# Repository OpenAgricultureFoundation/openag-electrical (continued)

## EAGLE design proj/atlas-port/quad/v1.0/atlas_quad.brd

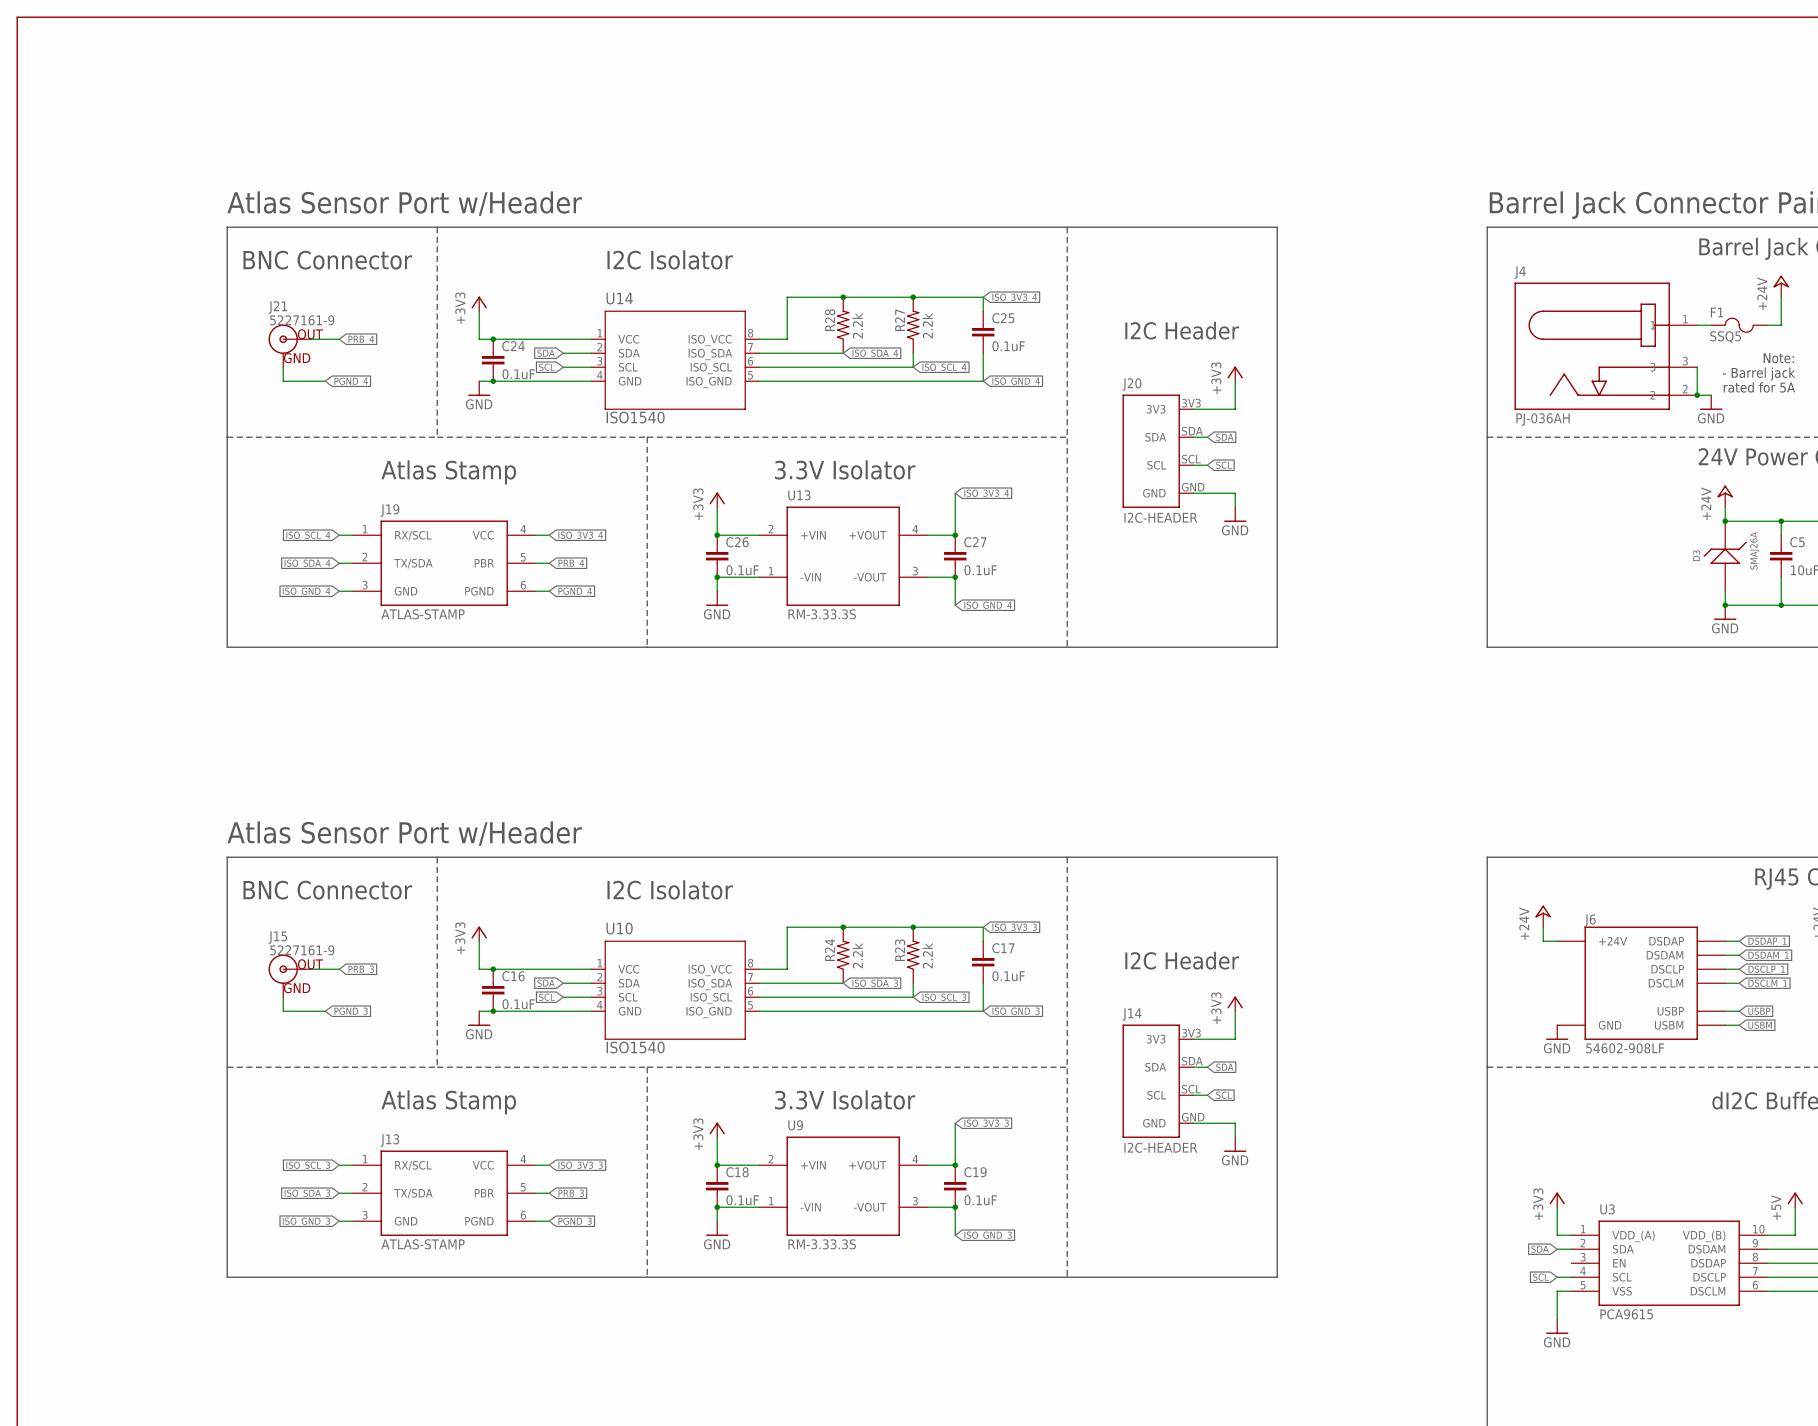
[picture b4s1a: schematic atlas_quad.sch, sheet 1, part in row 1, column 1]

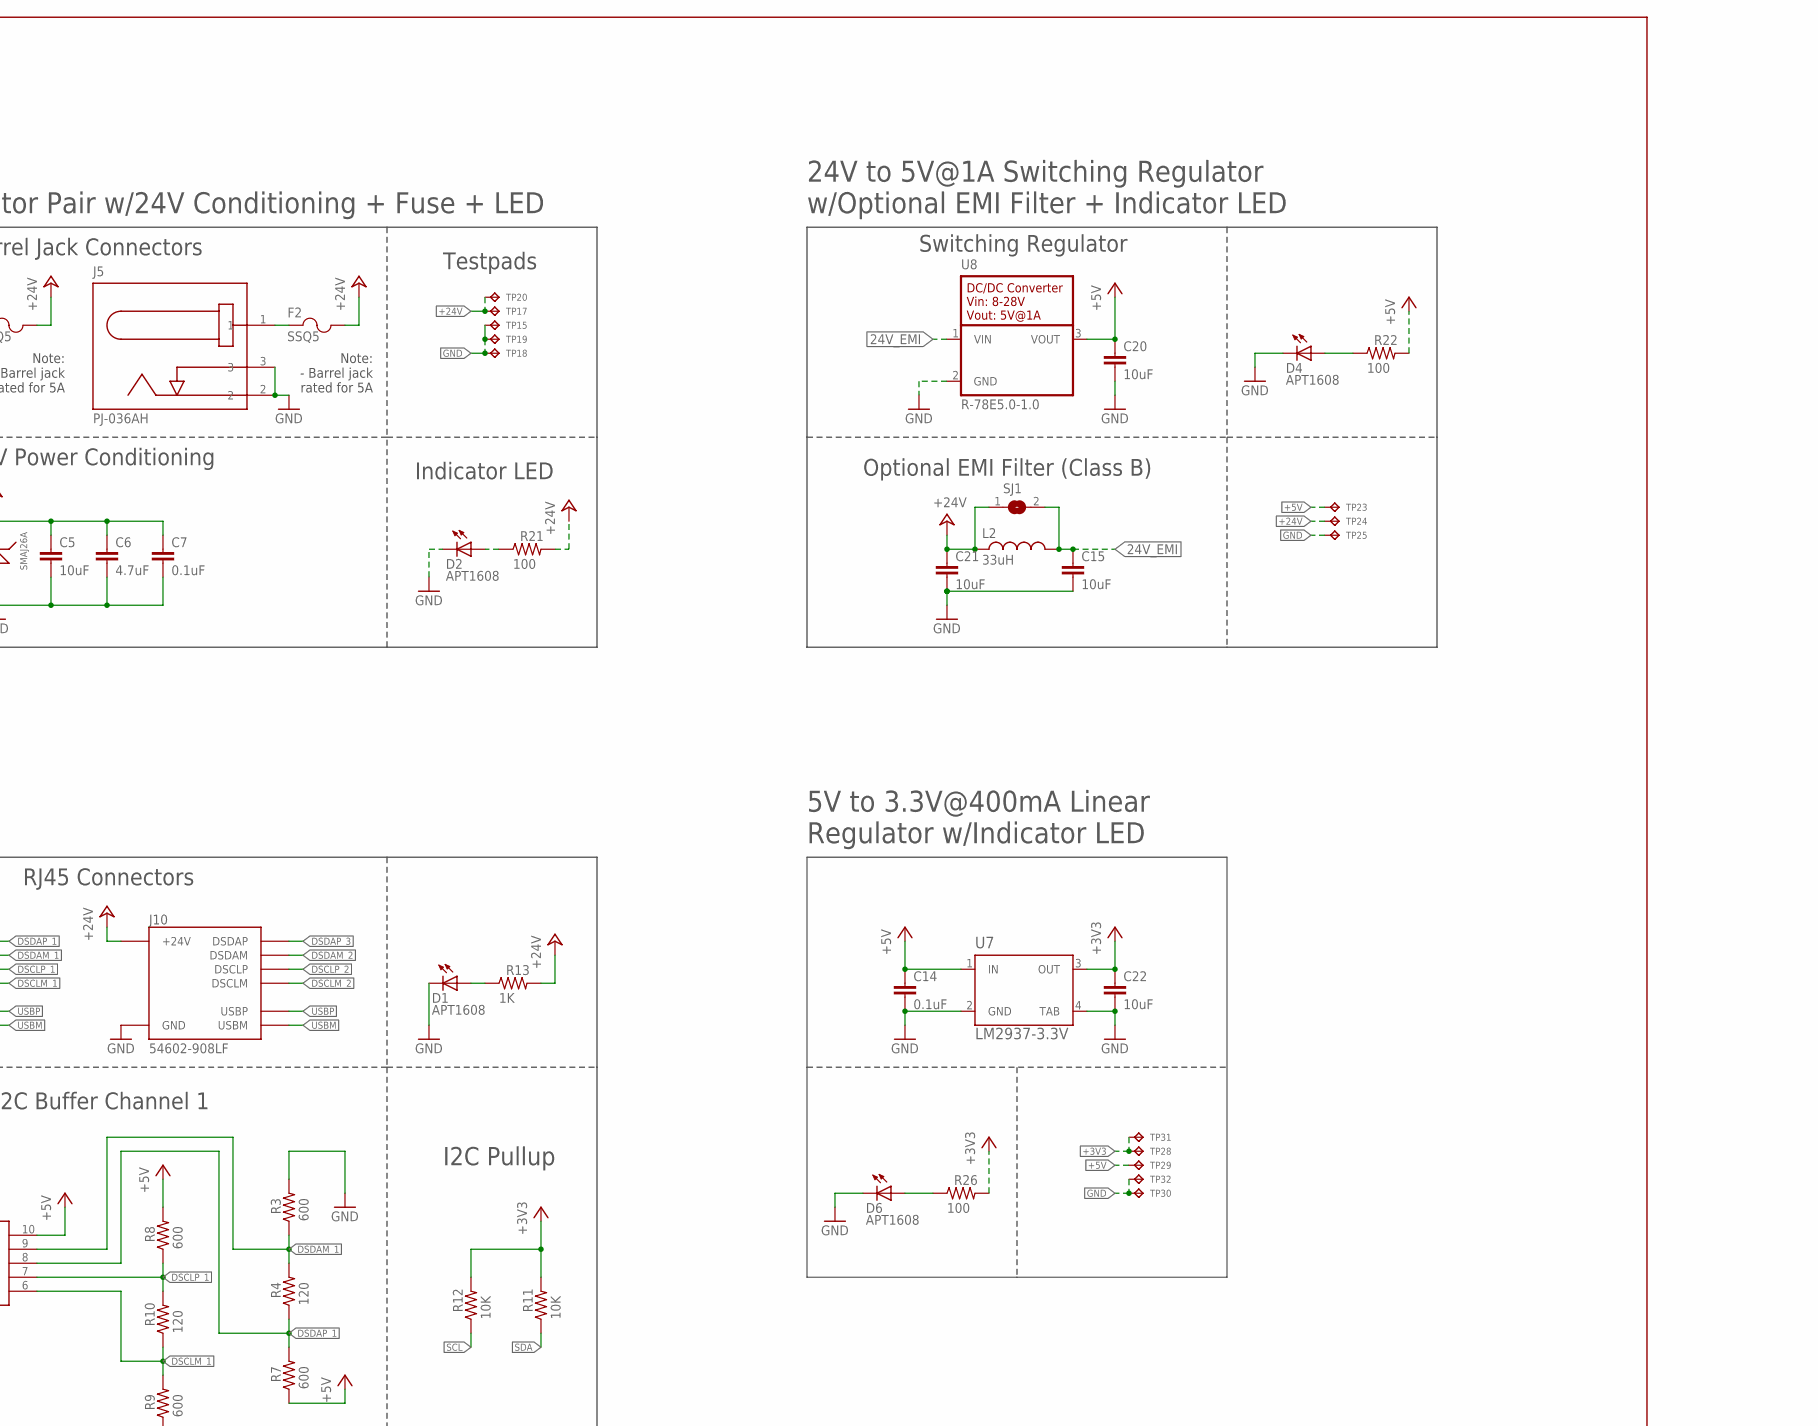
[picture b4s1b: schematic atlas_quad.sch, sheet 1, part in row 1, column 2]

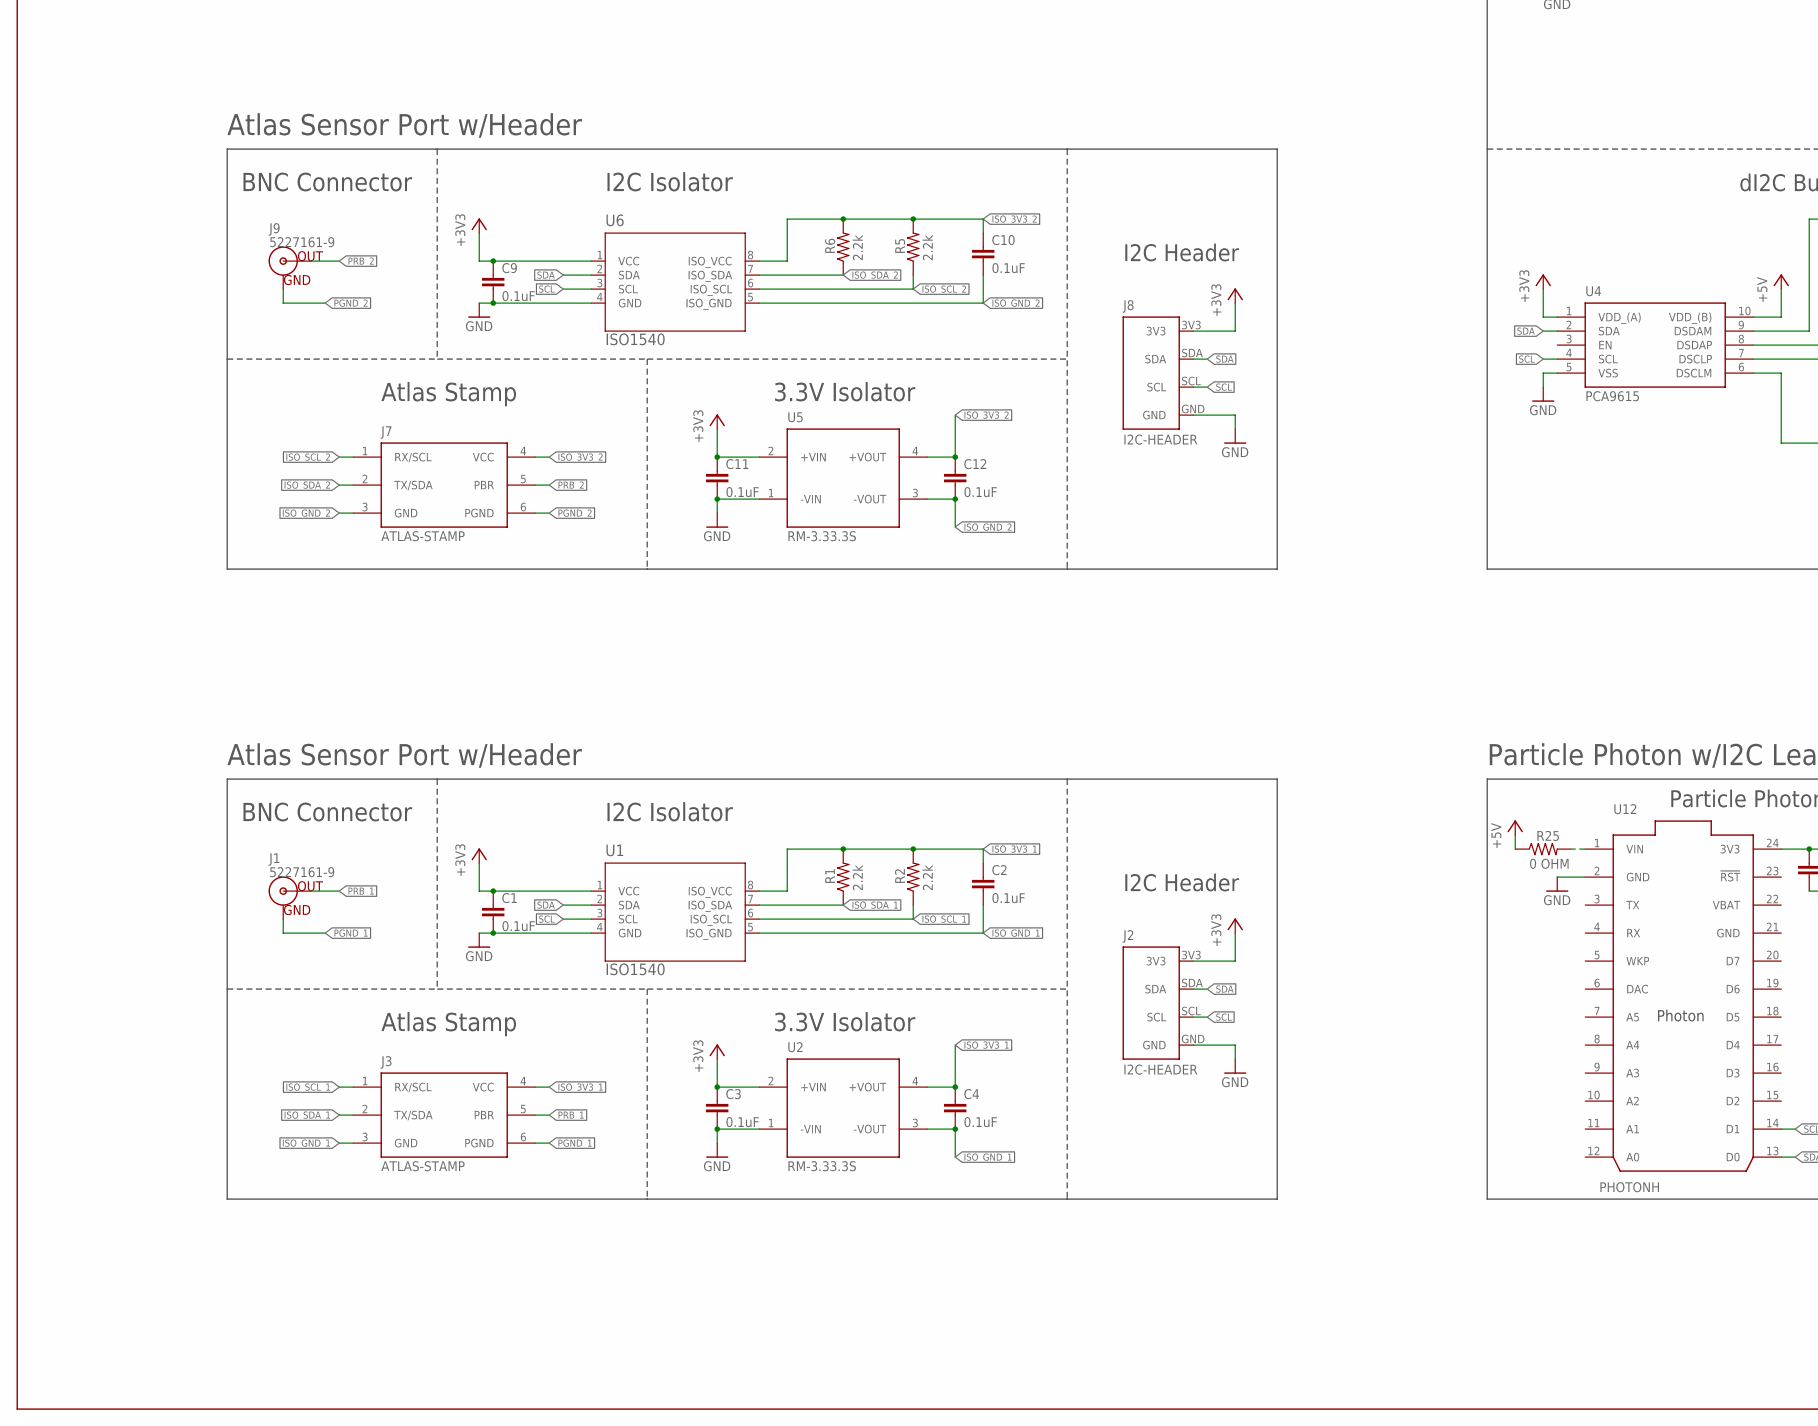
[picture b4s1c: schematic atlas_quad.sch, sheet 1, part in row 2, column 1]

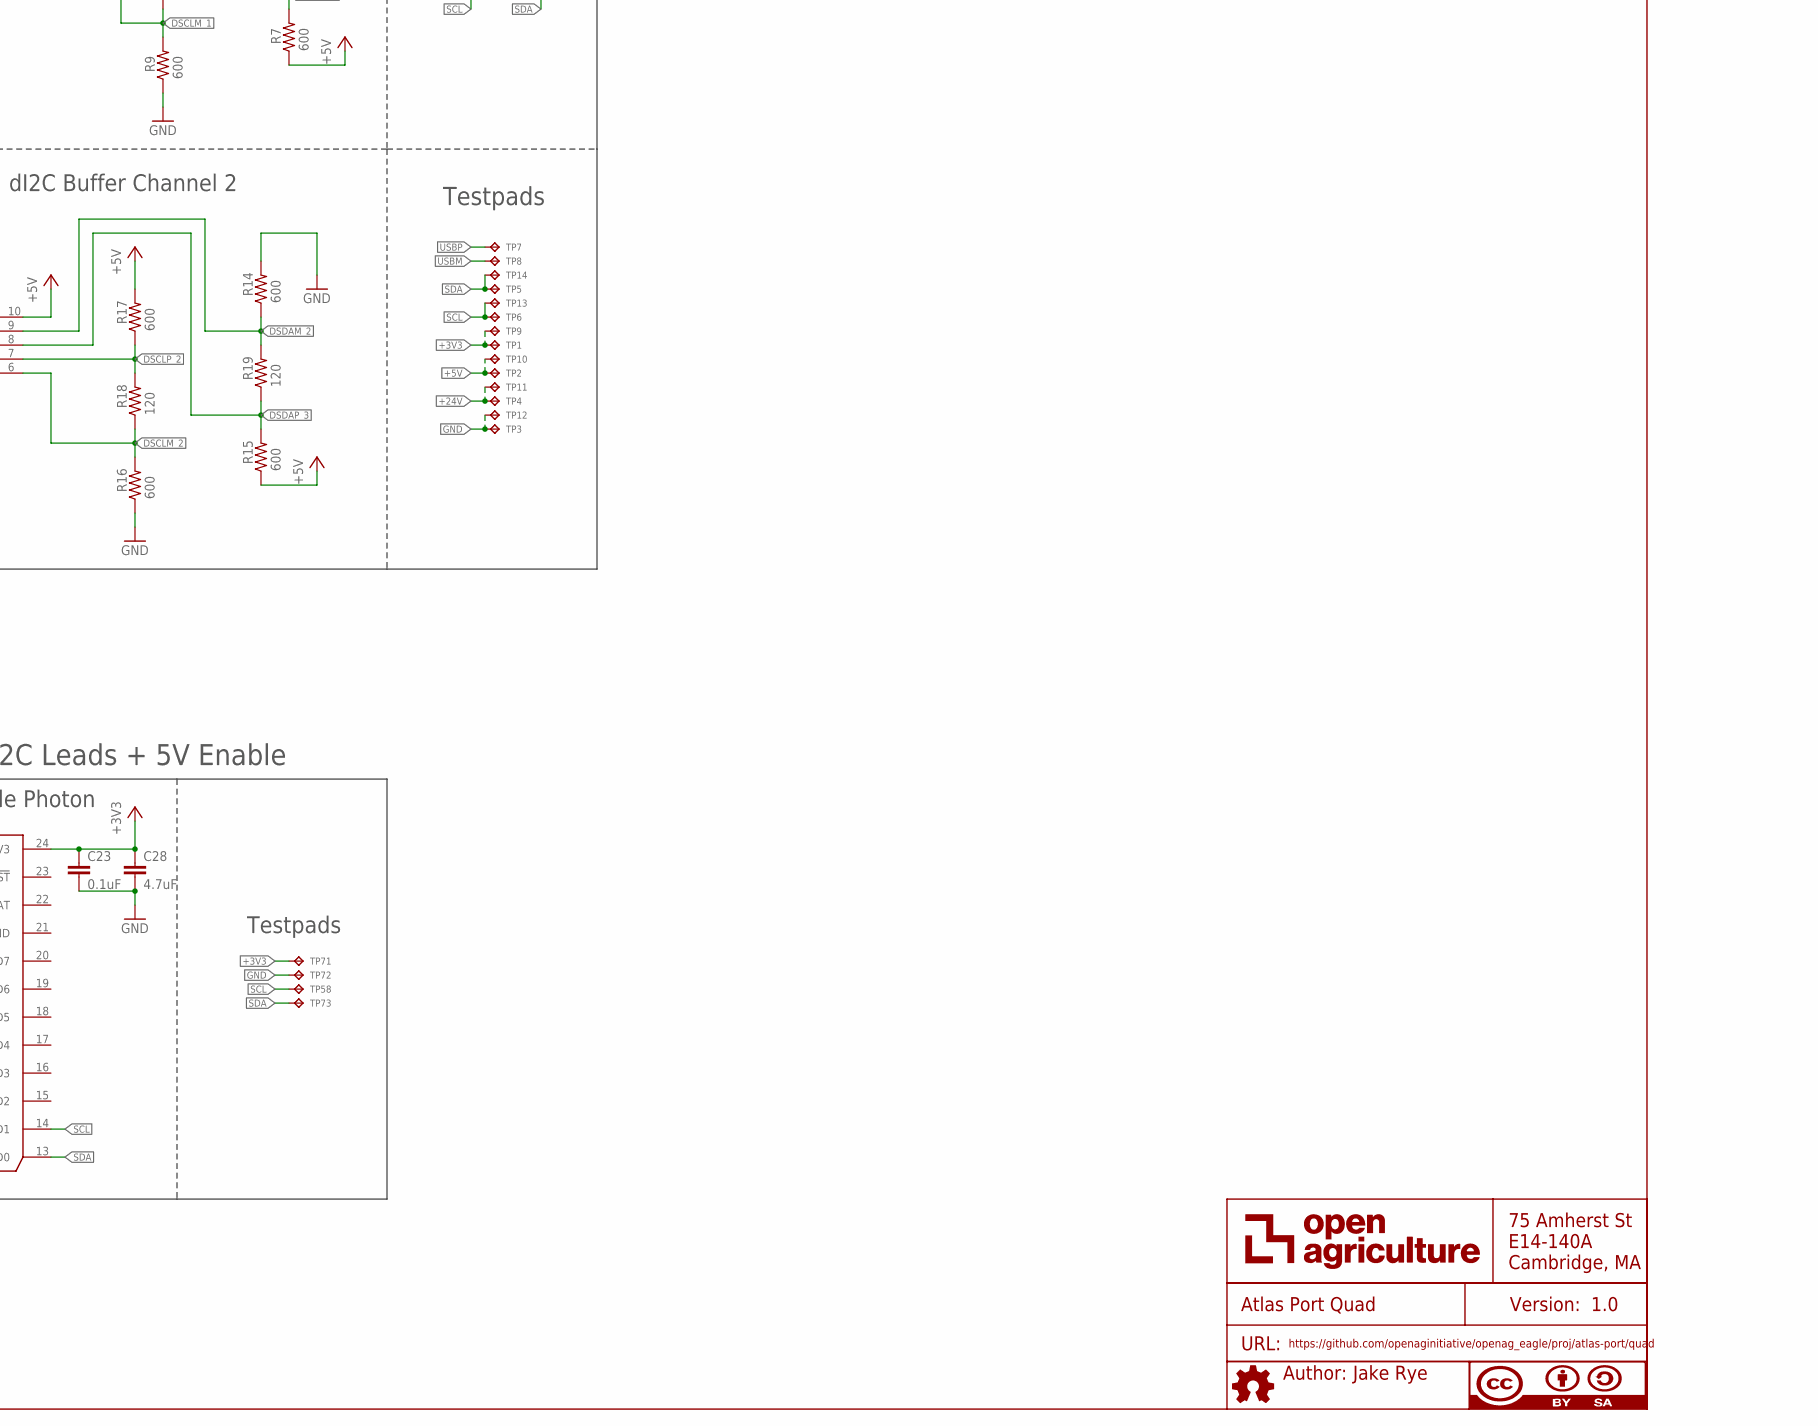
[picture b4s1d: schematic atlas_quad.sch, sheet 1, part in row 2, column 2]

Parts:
C1, C2, C3, C4, C7, C9, C10, C11, C12, C14, C16, C17, C18, C19, C23, C24, C25, C26, C27: 0.1uF; C0603
C5, C15, C20, C21, C22: 10uF; C0805
C6, C28: 4.7uF; C0805
D1, D2, D4, D6: APT1608; CHIPLED_0603
D3: SMAJ26A; SMA
F1, F2: SSQ5; SS
J1, J9, J15, J21: 5227161-9; BNC-5227161
J2, J8, J14, J20: I2C-HEADER; HEADER-I2C
J3, J7, J13, J19: ATLAS-STAMP
J4, J5: PJ-036AH; BARREL-JACK-PJ-036AH
J6, J10: 54602-908LF; RJ45-DI2C-USB-54602-908LF
L2: 33uH; 29333C
R1, R2, R5, R6, R23, R24, R27, R28: 2.2k; RC0603N
R3, R7, R8, R9, R14, R15, R16, R17: 600; RC0603N
R4, R10, R18, R19: 120; RC0603N
R11, R12: 10K; RC0603N
R13: 1K; RC0603N
R21, R22, R26: 100; RC0603N
R25: 0 OHM; RC0603N
SJ1: EMI-BYPASS
TP1, TP2, TP3, TP4, TP5, TP6, TP7, TP8, TP9, TP10, TP11, TP12, TP13, TP14, TP15, TP17, TP18, TP19, TP20, TP28, TP29, TP30, TP31, TP32, TP58, TP71, TP72, TP73: TPTP04R; TP04R
TP23, TP24, TP25: TPTP06R; TP06R
U1, U6, U10, U14: ISO1540; D8
U2, U5, U9, U13: RM-3.33.3S; RM3.33.3S-SIP4
U3, U4: PCA9615; SOP50P490X110-10N
U7: LM2937-3.3V; MP04A
U8: R-78E5.0-1.0
U12: PHOTONH; PHOTON
U$5: AUTHOR
U$6: TITLE

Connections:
24V_EMI: C15.1, L2.2, SJ1.2, U8.1 (VIN)
24V_IN1: F2.1, J5.1
24V_IN2: F1.1, J4.1
+3V3: C1.1, C3.1, C9.1, C11.1, C16.1, C18.1, C22.1, C23.1, C24.1, C26.1, C28.1, J2.3V3, J8.3V3, J14.3V3, J20.3V3, R11.2, R12.2, R26.2, TP1.1, TP9.1, TP28.1, TP31.1, TP71.1, U1.1 (VCC), U2.2 (+VIN), U3.1 (VDD_(A)), U4.1 (VDD_(A)), U5.2 (+VIN), U6.1 (VCC), U7.3 (OUT), U9.2 (+VIN), U10.1 (VCC), U12.24 (3V3), U13.2 (+VIN), U14.1 (VCC)
+5V: C14.1, C20.1, R7.1, R8.2, R15.1, R17.2, R22.2, R25.1, TP2.1, TP10.1, TP23.TP, TP29.1, U3.10 (VDD_(B)), U4.10 (VDD_(B)), U7.1 (IN), U8.3 (VOUT)
+24V: C5.1, C6.1, C7.1, C21.1, D3.1, F1.2, F2.2, J6.24V(6) (+24V), J10.24V(6) (+24V), L2.1, R13.2, R21.2, SJ1.1, TP4.1, TP11.1, TP17.1, TP20.1, TP24.TP
DSCLM_1: J6.DSCLM(5) (DSCLM), R9.2, R10.1, U3.6 (DSCLM)
DSCLM_2: J10.DSCLM(5) (DSCLM), R16.2, R18.1, U4.6 (DSCLM)
DSCLP_1: J6.DSCLP(4) (DSCLP), R8.1, R10.2, U3.7 (DSCLP)
DSCLP_2: J10.DSCLP(4) (DSCLP), R17.1, R18.2, U4.7 (DSCLP)
DSDAM_1: J6.DSDAM(2) (DSDAM), R3.1, R4.2, U3.9 (DSDAM)
DSDAM_2: J10.DSDAM(2) (DSDAM), R14.1, R19.2, U4.9 (DSDAM)
DSDAP_1: J6.DSDAP(1) (DSDAP), R4.1, R7.2, U3.8 (DSDAP)
DSDAP_3: J10.DSDAP(1) (DSDAP), R15.2, R19.1, U4.8 (DSDAP)
GND: C1.2, C3.2, C5.2, C6.2, C7.2, C9.2, C11.2, C14.2, C15.2, C16.2, C18.2, C20.2, C21.2, C22.2, C23.2, C24.2, C26.2, C28.2, D1.C, D2.C, D3.2, D4.C, D6.C, J2.GND, J4.2, J4.3, J5.2, J5.3, J6.GND(3) (GND), J8.GND, J10.GND(3) (GND), J14.GND, J20.GND, R3.2, R9.1, R14.2, R16.1, TP3.1, TP12.1, TP15.1, TP18.1, TP19.1, TP25.TP, TP30.1, TP32.1, TP72.1, U1.4 (GND), U2.1 (-VIN), U3.5 (VSS), U4.5 (VSS), U5.1 (-VIN), U6.4 (GND), U7.2 (GND), U7.4 (TAB), U8.2 (GND), U9.1 (-VIN), U10.4 (GND), U12.2 (GND), U12.21 (GND), U13.1 (-VIN), U14.4 (GND)
ISO_3V3_1: C2.1, C4.1, J3.4 (VCC), R1.2, R2.2, U1.8 (ISO_VCC), U2.4 (+VOUT)
ISO_3V3_2: C10.1, C12.1, J7.4 (VCC), R5.2, R6.2, U5.4 (+VOUT), U6.8 (ISO_VCC)
ISO_3V3_3: C17.1, C19.1, J13.4 (VCC), R23.2, R24.2, U9.4 (+VOUT), U10.8 (ISO_VCC)
ISO_3V3_4: C25.1, C27.1, J19.4 (VCC), R27.2, R28.2, U13.4 (+VOUT), U14.8 (ISO_VCC)
ISO_GND_1: C2.2, C4.2, J3.3 (GND), U1.5 (ISO_GND), U2.3 (-VOUT)
ISO_GND_2: C10.2, C12.2, J7.3 (GND), U5.3 (-VOUT), U6.5 (ISO_GND)
ISO_GND_3: C17.2, C19.2, J13.3 (GND), U9.3 (-VOUT), U10.5 (ISO_GND)
ISO_GND_4: C25.2, C27.2, J19.3 (GND), U13.3 (-VOUT), U14.5 (ISO_GND)
ISO_SCL_1: J3.1 (RX/SCL), R2.1, U1.6 (ISO_SCL)
ISO_SCL_2: J7.1 (RX/SCL), R5.1, U6.6 (ISO_SCL)
ISO_SCL_3: J13.1 (RX/SCL), R23.1, U10.6 (ISO_SCL)
ISO_SCL_4: J19.1 (RX/SCL), R27.1, U14.6 (ISO_SCL)
ISO_SDA_1: J3.2 (TX/SDA), R1.1, U1.7 (ISO_SDA)
ISO_SDA_2: J7.2 (TX/SDA), R6.1, U6.7 (ISO_SDA)
ISO_SDA_3: J13.2 (TX/SDA), R24.1, U10.7 (ISO_SDA)
ISO_SDA_4: J19.2 (TX/SDA), R28.1, U14.7 (ISO_SDA)
unnamed: R25.2, U12.1 (VIN)
unnamed: D1.A, R13.1
unnamed: D2.A, R21.1
unnamed: D4.A, R22.1
unnamed: D6.A, R26.1
PGND_1: J1.GND, J3.6 (PGND)
PGND_2: J7.6 (PGND), J9.GND
PGND_3: J13.6 (PGND), J15.GND
PGND_4: J19.6 (PGND), J21.GND
PRB_1: J1.S (OUT), J3.5 (PBR)
PRB_2: J7.5 (PBR), J9.S (OUT)
PRB_3: J13.5 (PBR), J15.S (OUT)
PRB_4: J19.5 (PBR), J21.S (OUT)
SCL: J2.SCL, J8.SCL, J14.SCL, J20.SCL, R12.1, TP6.1, TP13.1, TP58.1, U1.3 (SCL), U3.4 (SCL), U4.4 (SCL), U6.3 (SCL), U10.3 (SCL), U12.14 (D1), U14.3 (SCL)
SDA: J2.SDA, J8.SDA, J14.SDA, J20.SDA, R11.1, TP5.1, TP14.1, TP73.1, U1.2 (SDA), U3.2 (SDA), U4.2 (SDA), U6.2 (SDA), U10.2 (SDA), U12.13 (D0), U14.2 (SDA)
USBM: J6.USBM(8) (USBM), J10.USBM(8) (USBM), TP8.1
USBP: J6.USBP(7) (USBP), J10.USBP(7) (USBP), TP7.1
VBAT: U12.22 (VBAT)

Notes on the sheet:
3.3V Isolator
I2C Isolator
Atlas Stamp
BNC Connector
Atlas Sensor Port w/Header
I2C Header
dI2C Buffer Channel 1
RJ45 Connectors
dI2C Buffer Channel 2
Testpads
I2C Pullup
Barrel Jack Connectors
Barrel Jack Connector Pair w/24V Conditioning + Fuse + LED
24V Power Conditioning
Indicator LED
Note: - Barrel jack rated for 5A
Note: - Barrel jack rated for 5A
Particle Photon w/I2C Leads + 5V Enable
24V to 5V@1A Switching Regulator w/Optional EMI Filter + Indicator LED
Switching Regulator
Optional EMI Filter (Class B)
5V to 3.3V@400mA Linear Regulator w/Indicator LED
Particle Photon

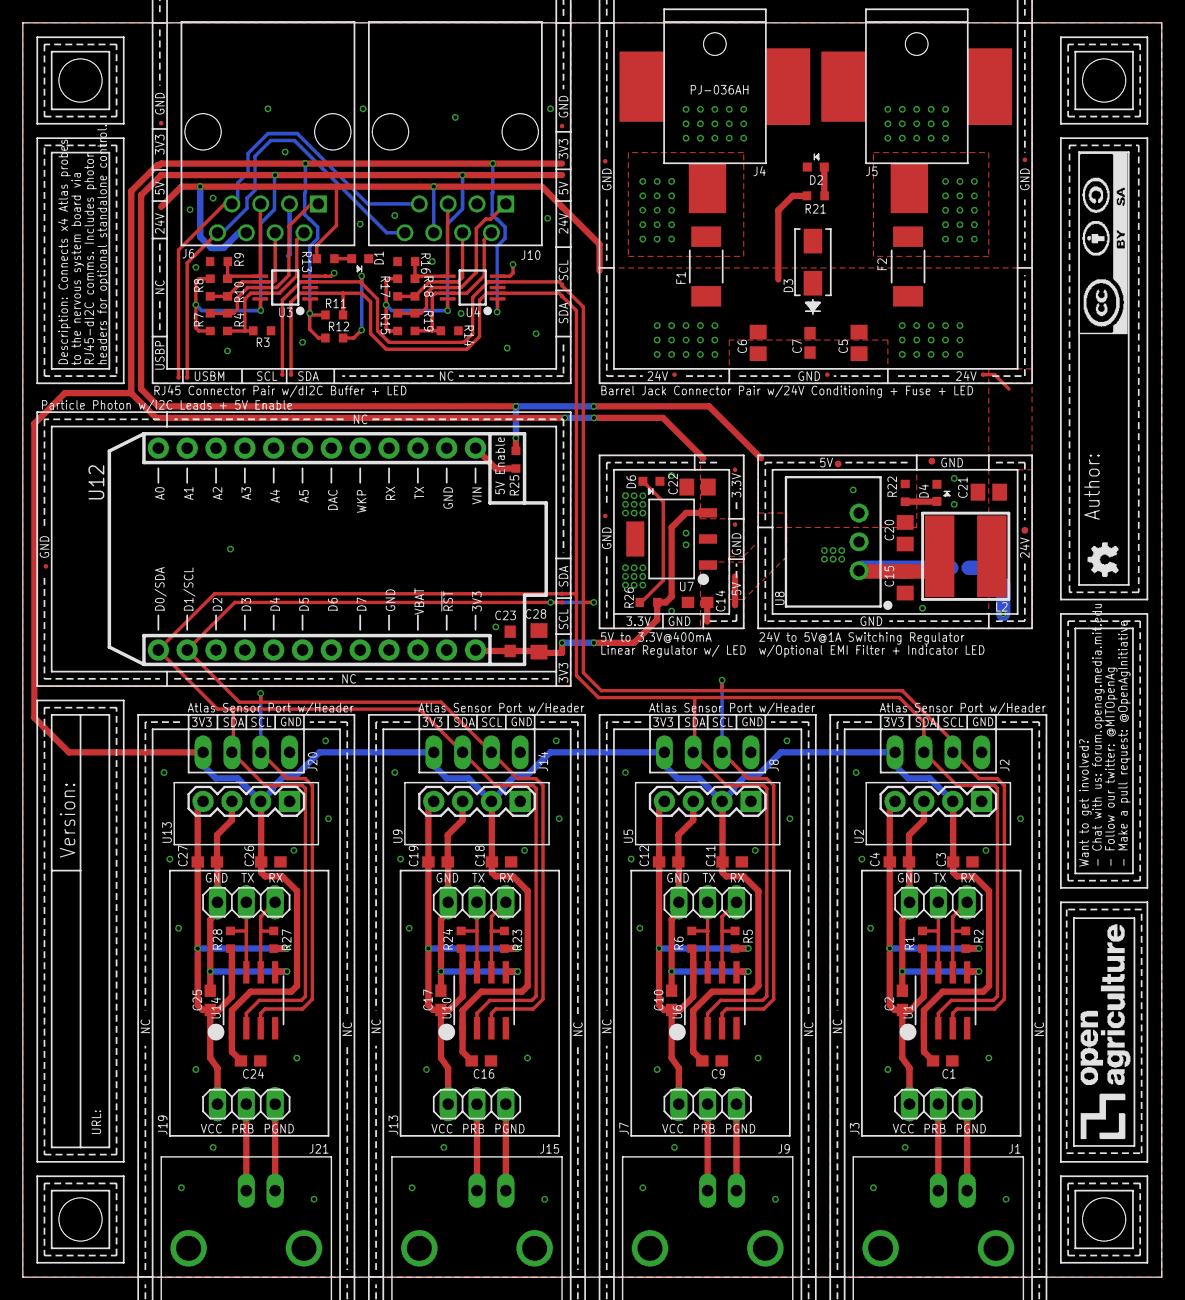
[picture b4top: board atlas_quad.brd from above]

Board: 2 copper layers, 100.3 x 110.5 mm, 129 parts (1 on the bottom side), 48 nets.

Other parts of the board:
U$1, U$2, U$3, U$4: CORNER-150
U$8: LOGO-900X300

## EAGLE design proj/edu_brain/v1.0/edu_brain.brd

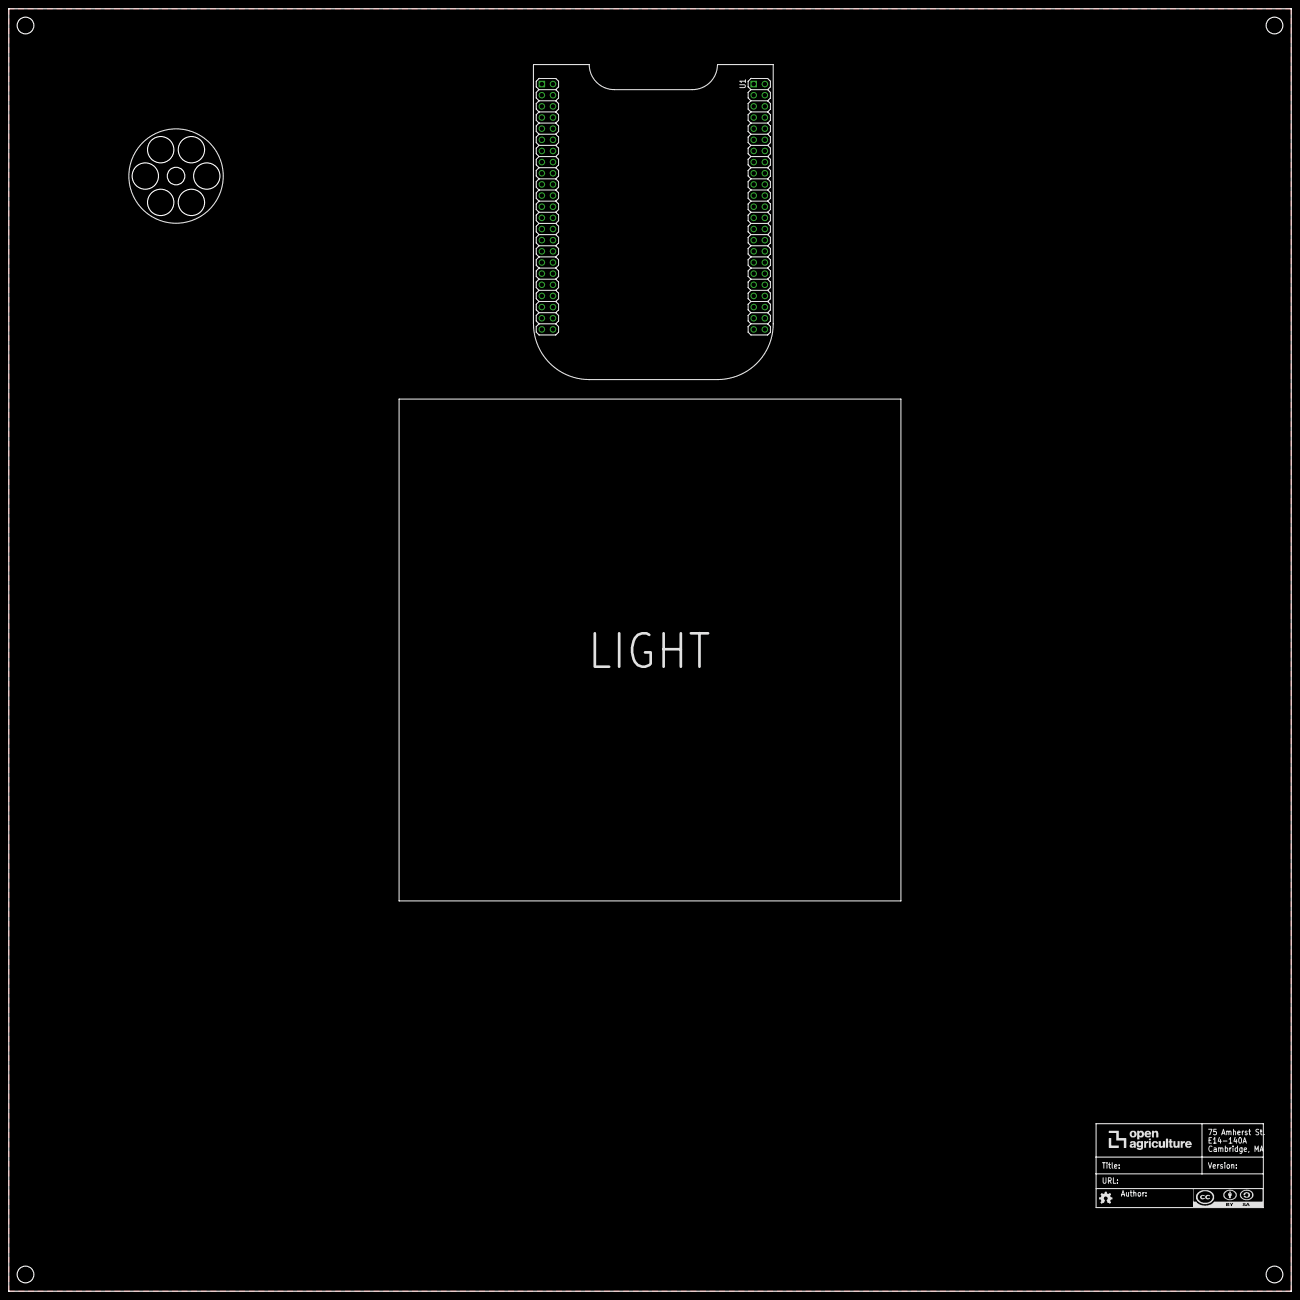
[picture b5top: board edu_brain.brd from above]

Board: 2 copper layers, 292.1 x 292.1 mm, 7 parts (0 on the bottom side), 3 nets, no tracks yet.

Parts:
FRAME1: DOCFIELD
U1: BEAGLEBONE_OUTLINE; BEAGLEBONE_SHIELD
U$1, U$2, U$3, U$4: OPENAG-CORNER-MOUNTING-HOLE
U$5: UMBRELLA-VALVE-21.5MM

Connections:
GND: U1.1, U1.2, U1.47, U1.48, U1.89, U1.90, U1.91, U1.92
VDD_3V3EXP: U1.49, U1.50
VDD_5V: U1.51, U1.52
